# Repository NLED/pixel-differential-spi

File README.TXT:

THERE IS NO WARRANTY FOR THE PROGRAM, TO THE EXTENT PERMITTED BY APPLICABLE LAW. 
EXCEPT WHEN OTHERWISE STATED IN WRITING THE COPYRIGHT HOLDERS AND/OR OTHER PARTIES 
PROVIDE THE PROGRAM “AS IS” WITHOUT WARRANTY OF ANY KIND, EITHER EXPRESSED OR IMPLIED,
INCLUDING, BUT NOT LIMITED TO, THE IMPLIED WARRANTIES OF MERCHANTABILITY AND FITNESS 
FOR A PARTICULAR PURPOSE. THE ENTIRE RISK AS TO THE QUALITY AND PERFORMANCE OF THE 
PROGRAM IS WITH YOU. SHOULD THE PROGRAM PROVE DEFECTIVE, YOU ASSUME THE COST OF ALL 
NECESSARY SERVICING, REPAIR OR CORRECTION.

 Original Author: Jeffrey Nygaard
 Company: Northern Lights Electronic Design, LLC
 Date: July 26, 2018
 Contact: JNygaard@NLEDshop.com
 Copyright© 2018 by Northern Lights Electronic Design, LLC. All Rights Reserved
 
;=============          www.NLEDShop.com/miscproducts          ============
;=============     www.NorthernLightsElectronicDesign.com       ============

This work is licensed under a Attribution-NonCommercial 4.0 International (CC BY-NC 4.0)
https://creativecommons.org/licenses/by-nc/4.0/legalcode

Free to use for personal use, but please attribute the original author.

Commercial licenses versions are available for a donation of any amount. Contact JNygaard@NLEDshop.com for details.

================================================================================================================

Ready-made devices are available for purchase, and large batch manufacturing of any device can be requested.
Please see the webpage www.NLEDShop.com/miscproducts

NLED is available for custom design and manufacturing, please contact via phone or email to discuss your project.

================================================================================================================

Converts TTL SPI signals into differential signals and back to TTL SPI. Useful for long distance SPI communication with
various LED pixels and other unidirection SPI devices.

Minimum Input Voltage: 5 volts
Maximum Input Voltage: 12 volts
Current Consumption: < 80mA estimated

Jumper settings:
TERM1: Signal termination. Close jumper if that channel is receiving
TERM2: Signal termination. Close jumper if that channel is receiving
DIR-J: Sets transcievers for reception or transmission. Tie center pad to R to set for reception. Tie center pad to T for transmission.
TRANS-1-J: Selects transmission or reception for channel #1. Tie to T for transmit, or R for reception
TRANS-2-J: Selects transmission or reception for channel #2. Tie to T for transmit, or R for reception
VREG-J: If using 5 volt power input, close the jumper. If using an input voltage larger than 5 volts, leave jumper open. Max input voltage is 12 volts. 

BOM:
2x SN75176BDR - SOIC-8 - or equivelent differntial transceiver
1x AP2210K-5.0TRG1 - SOT-23-5 - 5 volt linear regulator
2x 120 ohm resistor - 0805 - termination resistors
1x 1uF to 10uF >=6.3vdc - 0805 - tank capacitance
1x 100pF >=6.3vdc - 0805 - voltage regulator bypass
2x 0.1uF >=6.3vdc - 0805 - transceiver decouple

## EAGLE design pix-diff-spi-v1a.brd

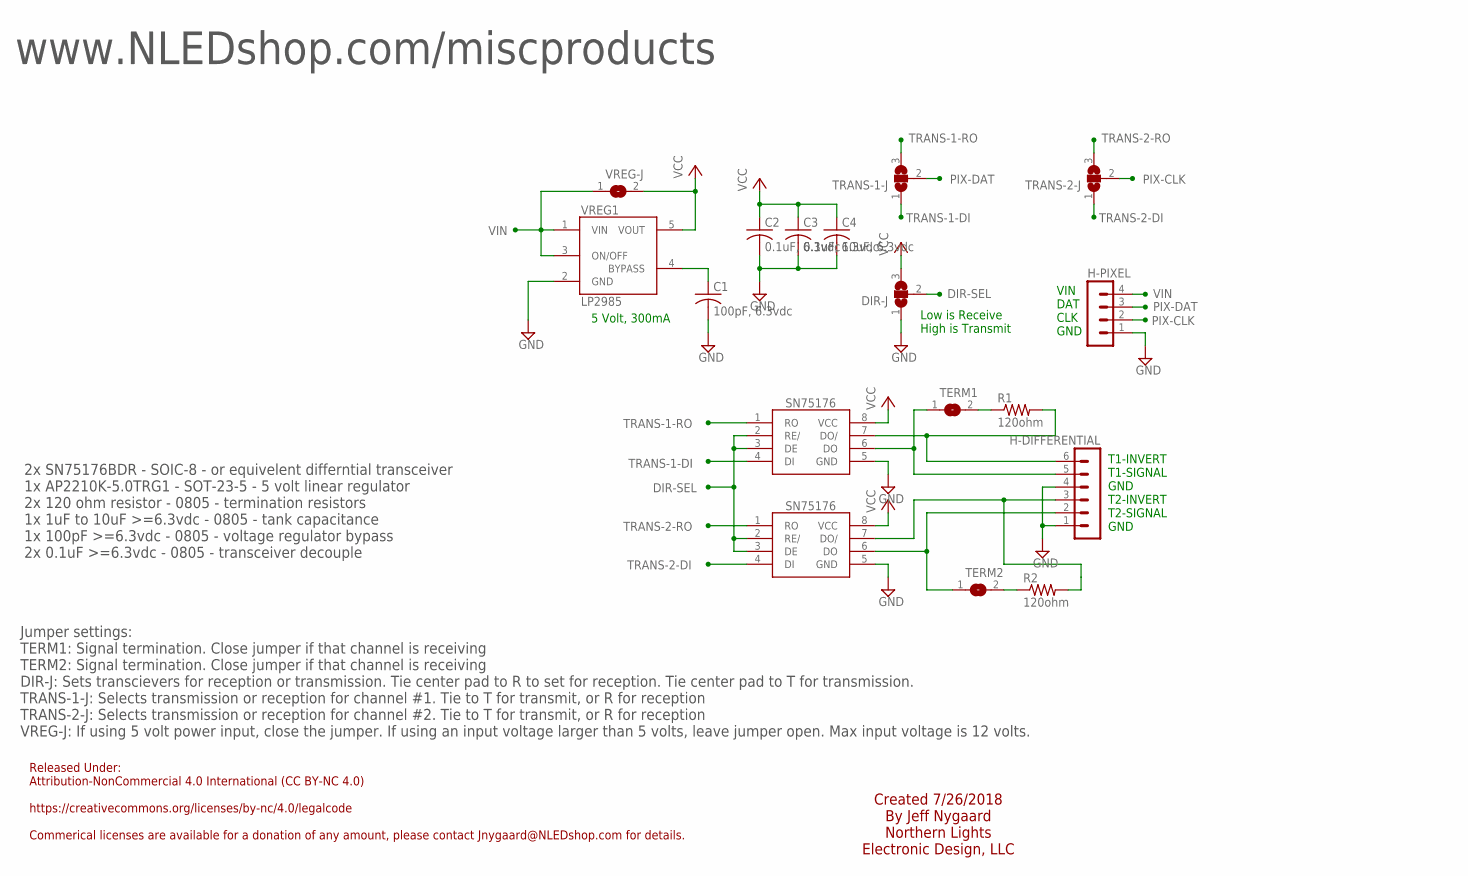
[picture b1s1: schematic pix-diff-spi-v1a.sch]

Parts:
C1: 100pF, 6.3vdc; C0805
C2, C3: 0.1uF, 6.3vdc; C0805
C4: 10uF, 6.3vdc; C0805
DIR-J: SJ2W; SJ_2
H-DIFFERENTIAL: MA06-1
H-PIXEL: MA04-1
R1, R2: 120ohm; R0805
TERM1, TERM2: SJ
TRANS1, TRANS2: SN75176SMD; SOIC-8
TRANS-1-J, TRANS-2-J: SJ2W; SJ_2
VREG1: LP2985AIM5-3.3; SOT25
VREG-J: SJ

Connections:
BYPASS: C1.1, VREG1.4 (BYPASS)
DIR-SEL: DIR-J.2, TRANS1.2 (RE/), TRANS1.3 (DE), TRANS2.2 (RE/), TRANS2.3 (DE)
GND: C1.2, C2.2, C3.2, C4.2, DIR-J.1, H-DIFFERENTIAL.1, H-DIFFERENTIAL.4, H-PIXEL.1, TRANS1.5 (GND), TRANS2.5 (GND), VREG1.2 (GND)
unnamed: R1.1, TERM1.2
unnamed: R2.1, TERM2.2
PIX-CLK: H-PIXEL.2, TRANS-2-J.2
PIX-DAT: H-PIXEL.3, TRANS-1-J.2
T1-INVERT: H-DIFFERENTIAL.6, R1.2, TRANS1.7 (DO/)
T1-SIGNAL: H-DIFFERENTIAL.5, TERM1.1, TRANS1.6 (DO)
T2-INVERT: H-DIFFERENTIAL.3, R2.2, TRANS2.7 (DO/)
T2-SIGNAL: H-DIFFERENTIAL.2, TERM2.1, TRANS2.6 (DO)
TRANS-1-DI: TRANS1.4 (DI), TRANS-1-J.1
TRANS-1-RO: TRANS1.1 (RO), TRANS-1-J.3
TRANS-2-DI: TRANS2.4 (DI), TRANS-2-J.1
TRANS-2-RO: TRANS2.1 (RO), TRANS-2-J.3
VCC: C2.1, C3.1, C4.1, DIR-J.3, TRANS1.8 (VCC), TRANS2.8 (VCC), VREG1.5 (VOUT), VREG-J.2
VIN: H-PIXEL.4, VREG1.1 (VIN), VREG1.3 (ON/OFF), VREG-J.1

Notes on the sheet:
Low is Receive High is Transmit
VIN DAT CLK GND
T1-INVERT T1-SIGNAL GND T2-INVERT T2-SIGNAL GND
Created 7/26/2018 By Jeff Nygaard Northern Lights Electronic Design, LLC
Released Under: Attribution-NonCommercial 4.0 International (CC BY-NC 4.0) https://creativecommons.org/licenses/by-nc/4.0/legalcode Commerical licenses are available for a donation of any amount, please contact Jnygaard@NLEDshop.com for details.
5 Volt, 300mA
Jumper settings: TERM1: Signal termination. Close jumper if that channel is receiving TERM2: Signal termination. Close jumper if that channel is receiving DIR-J: Sets transcievers for reception or transmission. Tie center pad to R to set for reception. Tie center pad to T for transmission. TRANS-1-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
2x SN75176BDR - SOIC-8 - or equivelent differntial transceiver 1x AP2210K-5.0TRG1 - SOT-23-5 - 5 volt linear regulator 2x 120 ohm resistor - 0805 - termination resistors 1x 1uF to 10uF >=6.3vdc - 0805 - tank capacitance 1x 100pF >=6.3vdc - 0805 - voltage regulator bypass 2x 0.1uF >=6.3vdc - 0805 - 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
www.NLEDshop.com/miscproducts

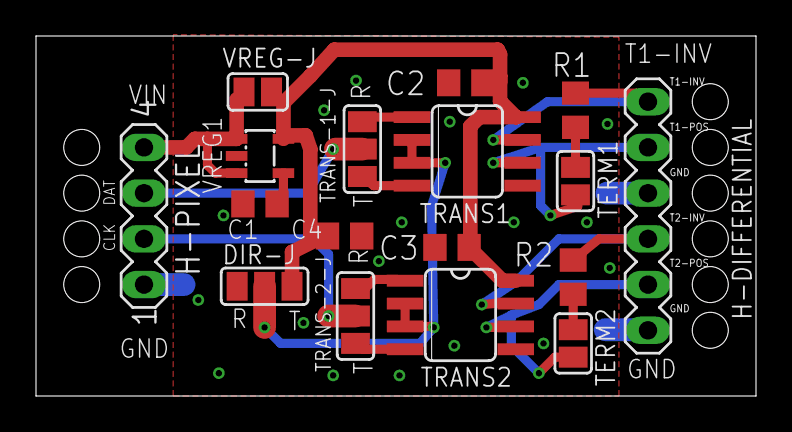
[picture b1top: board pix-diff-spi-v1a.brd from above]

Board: 2 copper layers, 40.0 x 20.0 mm, 17 parts (0 on the bottom side), 17 nets.

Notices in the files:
pix-diff-spi-v1a.brd:
Copyright 2018
